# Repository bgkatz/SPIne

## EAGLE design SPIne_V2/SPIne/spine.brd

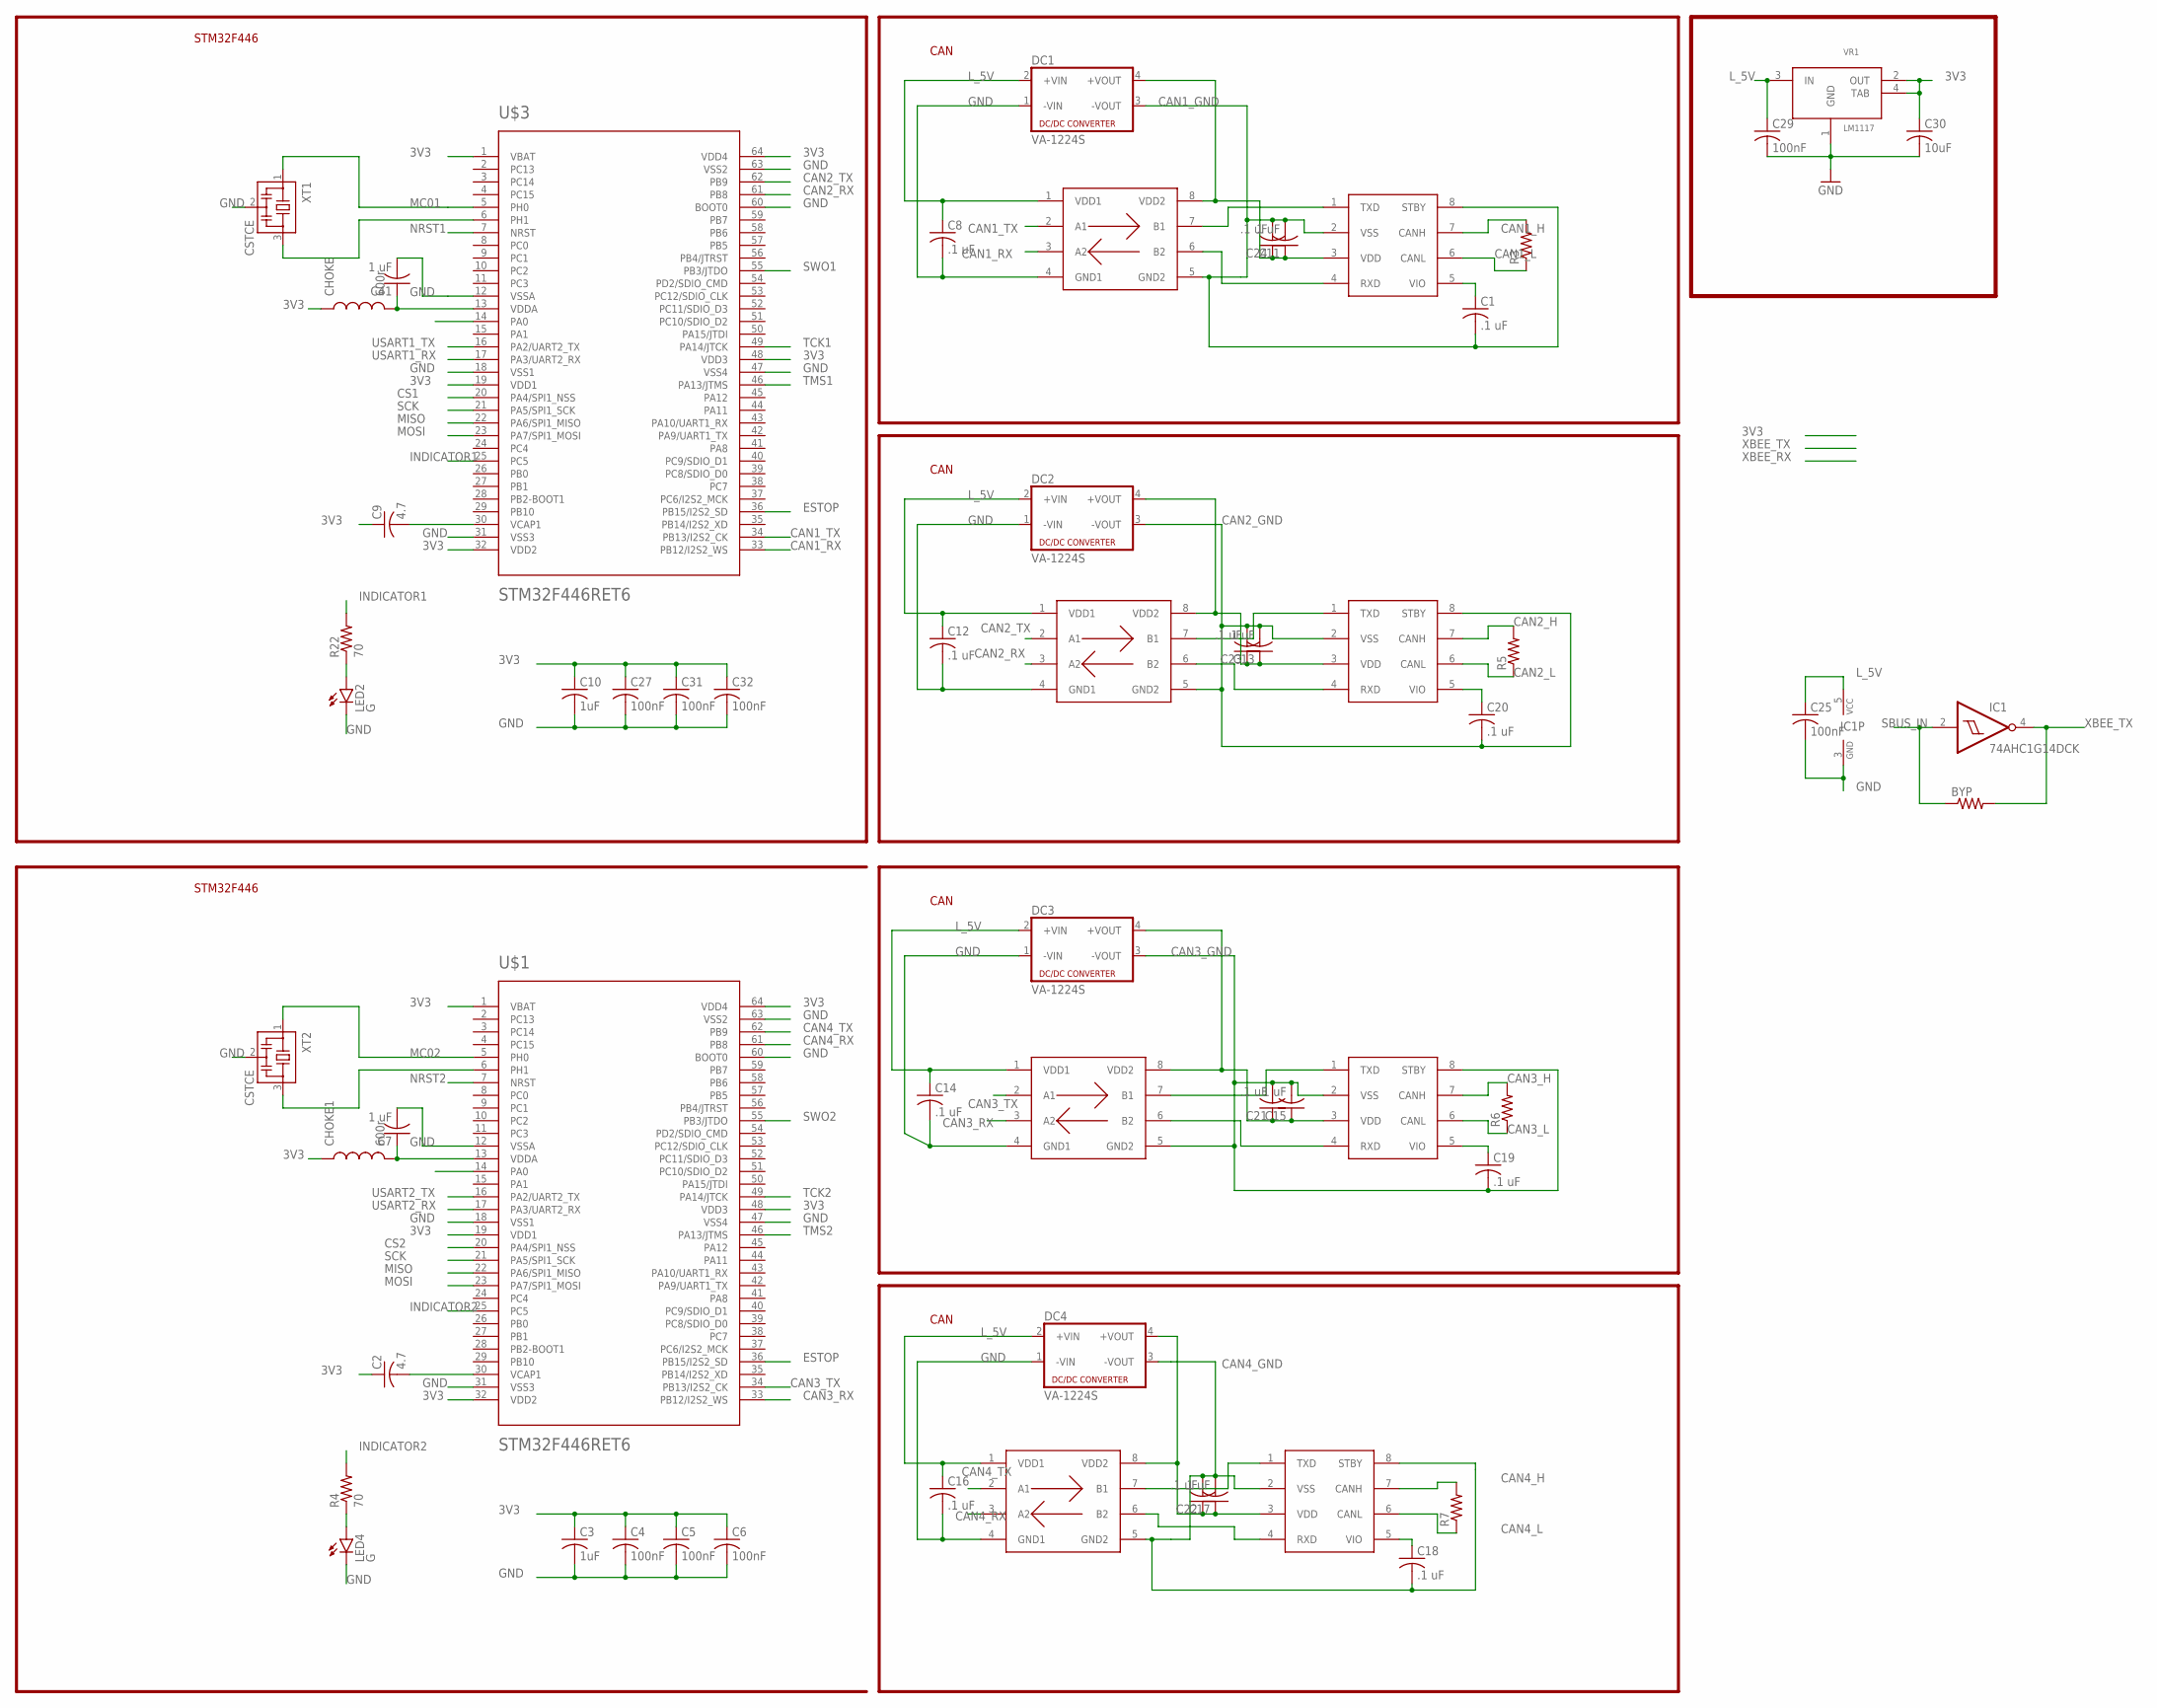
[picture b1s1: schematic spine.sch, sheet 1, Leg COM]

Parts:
BYP: R-US_R0402; R0402
C1, C8, C12, C14, C16, C18, C19, C20, C21, C22, C23, C24: .1 uF; C0603K
C2, C9: 4.7; C0603
C3, C10: 1uF; C0603
C4, C5, C6, C25, C27, C29, C31, C32: 100nF; C0603
C7, C41: 1 uF; C0603
C11, C13, C15, C17: 1 uF; C0603K
C30: 10uF; C0805K
CHOKE, CHOKE1: 600r; 0603
DC1, DC2, DC3, DC4: VA-1224S; 4SIL
IC1: 74AHC1G14DCK; SC70-5
LED2, LED4: G; LED-0603
R3, R5, R6, R7: R-US_R0402; R0402
R4, R22: 70; R0603
U$1, U$3: STM32F446RET6; TQFP64
U$4, U$5, U$6, U$7: MCP2561; SO08
U$8, U$9, U$10, U$11: SI8410; SO08
VR1: LM1117; SOT-223
XT1, XT2: CSTCE

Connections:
3V3: C2.1, C3.1, C4.1, C5.1, C6.1, C9.1, C10.1, C27.1, C30.1, C31.1, C32.1, CHOKE.1, CHOKE1.1, U$1.1 (VBAT), U$1.19 (VDD1), U$1.32 (VDD2), U$1.48 (VDD3), U$1.64 (VDD4), U$3.1 (VBAT), U$3.19 (VDD1), U$3.32 (VDD2), U$3.48 (VDD3), U$3.64 (VDD4), VR1.2 (OUT), VR1.4 (TAB); also elsewhere on the board
': C17.1, C22.1, DC4.4 (+VOUT), U$7.3 (VDD), U$11.8 (VDD2)
CAN1_GND: C1.2, C11.2, C24.2, DC1.3 (-VOUT), U$4.2 (VSS), U$4.8 (STBY), U$8.5 (GND2); also elsewhere on the board
CAN1_H: R3.2, U$4.7 (CANH); also elsewhere on the board
CAN1_L: R3.1, U$4.6 (CANL); also elsewhere on the board
CAN1_RX: U$3.33 (PB12/I2S2_WS), U$8.3 (A2)
CAN1_TX: U$3.34 (PB13/I2S2_CK), U$8.2 (A1)
CAN2_GND: C13.2, C20.2, C23.2, DC2.3 (-VOUT), U$5.2 (VSS), U$5.8 (STBY), U$10.5 (GND2); also elsewhere on the board
CAN2_H: R5.2, U$5.7 (CANH); also elsewhere on the board
CAN2_L: R5.1, U$5.6 (CANL); also elsewhere on the board
CAN2_RX: U$3.61 (PB8), U$10.3 (A2)
CAN2_TX: U$3.62 (PB9), U$10.2 (A1)
CAN3_GND: C15.2, C19.2, C21.2, DC3.3 (-VOUT), U$6.2 (VSS), U$6.8 (STBY), U$9.5 (GND2); also elsewhere on the board
CAN3_H: R6.2, U$6.7 (CANH); also elsewhere on the board
CAN3_L: R6.1, U$6.6 (CANL); also elsewhere on the board
CAN3_RX: U$1.33 (PB12/I2S2_WS), U$9.3 (A2)
CAN3_TX: U$1.34 (PB13/I2S2_CK), U$9.2 (A1)
CAN4_GND: C17.2, C18.2, C22.2, DC4.3 (-VOUT), U$7.2 (VSS), U$7.8 (STBY), U$11.5 (GND2); also elsewhere on the board
CAN4_H: R7.2, U$7.7 (CANH); also elsewhere on the board
CAN4_L: R7.1, U$7.6 (CANL); also elsewhere on the board
CAN4_RX: U$1.61 (PB8), U$11.3 (A2)
CAN4_TX: U$1.62 (PB9), U$11.2 (A1)
CS1: U$3.20 (PA4/SPI1_NSS); also elsewhere on the board
CS2: U$1.20 (PA4/SPI1_NSS); also elsewhere on the board
ESTOP: U$1.36 (PB15/I2S2_SD), U$3.36 (PB15/I2S2_SD); also elsewhere on the board
GND: C3.2, C4.2, C5.2, C6.2, C7.2, C8.2, C10.2, C12.2, C14.2, C16.2, C25.2, C27.2, C29.2, C30.2, C31.2, C32.2, C41.2, DC1.1 (-VIN), DC2.1 (-VIN), DC3.1 (-VIN), DC4.1 (-VIN), IC1.3 (GND), LED2.C, LED4.C, U$1.12 (VSSA), U$1.18 (VSS1), U$1.31 (VSS3), U$1.47 (VSS4), U$1.60 (BOOT0), U$1.63 (VSS2), U$3.12 (VSSA), U$3.18 (VSS1), U$3.31 (VSS3), U$3.47 (VSS4), U$3.60 (BOOT0), U$3.63 (VSS2), U$8.4 (GND1), U$9.4 (GND1), U$10.4 (GND1), U$11.4 (GND1), VR1.1 (GND), XT1.2, XT2.2; also elsewhere on the board
INDICATOR1: R22.2, U$3.25 (PC5)
INDICATOR2: R4.2, U$1.25 (PC5)
L_5V: C8.1, C12.1, C14.1, C16.1, C25.1, C29.1, DC1.2 (+VIN), DC2.2 (+VIN), DC3.2 (+VIN), DC4.2 (+VIN), IC1.5 (VCC), U$8.1 (VDD1), U$9.1 (VDD1), U$10.1 (VDD1), U$11.1 (VDD1), VR1.3 (IN); also elsewhere on the board
MC01: U$3.5 (PH0), XT1.1
MC02: U$1.5 (PH0), XT2.1
MISO: U$1.22 (PA6/SPI1_MISO), U$3.22 (PA6/SPI1_MISO); also elsewhere on the board
MOSI: U$1.23 (PA7/SPI1_MOSI), U$3.23 (PA7/SPI1_MOSI); also elsewhere on the board
unnamed: C41.1, CHOKE.2, U$3.13 (VDDA)
unnamed: C9.2, U$3.30 (VCAP1)
unnamed: C7.1, CHOKE1.2, U$1.13 (VDDA)
unnamed: C2.2, U$1.30 (VCAP1)
unnamed: C1.1, U$4.5 (VIO)
unnamed: LED4.A, R4.1
unnamed: U$1.6 (PH1), XT2.3
unnamed: C20.1, U$5.5 (VIO)
unnamed: C15.1, C21.1, DC3.4 (+VOUT), U$6.3 (VDD), U$9.8 (VDD2)
unnamed: C11.1, C24.1, DC1.4 (+VOUT), U$4.3 (VDD), U$8.8 (VDD2)
unnamed: U$4.1 (TXD), U$8.7 (B1)
unnamed: U$7.1 (TXD), U$11.7 (B1)
unnamed: U$4.4 (RXD), U$8.6 (B2)
unnamed: U$7.4 (RXD), U$11.6 (B2)
unnamed: C18.1, U$7.5 (VIO)
unnamed: C13.1, C23.1, DC2.4 (+VOUT), U$5.3 (VDD), U$10.8 (VDD2)
unnamed: U$5.1 (TXD), U$10.7 (B1)
unnamed: U$5.4 (RXD), U$10.6 (B2)
unnamed: C19.1, U$6.5 (VIO)
unnamed: U$6.1 (TXD), U$9.7 (B1)
unnamed: U$6.4 (RXD), U$9.6 (B2)
unnamed: LED2.A, R22.1
unnamed: U$3.6 (PH1), XT1.3
NRST1: U$3.7 (NRST); also elsewhere on the board
NRST2: U$1.7 (NRST); also elsewhere on the board
SBUS_IN: BYP.1, IC1.2 (I); also elsewhere on the board
SCK: U$1.21 (PA5/SPI1_SCK), U$3.21 (PA5/SPI1_SCK); also elsewhere on the board
SWO1: U$3.55 (PB3/JTDO)
SWO2: U$1.55 (PB3/JTDO)
TCK1: U$3.49 (PA14/JTCK); also elsewhere on the board
TCK2: U$1.49 (PA14/JTCK); also elsewhere on the board
TMS1: U$3.46 (PA13/JTMS); also elsewhere on the board
TMS2: U$1.46 (PA13/JTMS); also elsewhere on the board
USART1_RX: U$3.17 (PA3/UART2_RX); also elsewhere on the board
USART1_TX: U$3.16 (PA2/UART2_TX); also elsewhere on the board
USART2_RX: U$1.17 (PA3/UART2_RX); also elsewhere on the board
USART2_TX: U$1.16 (PA2/UART2_TX); also elsewhere on the board
XBEE_TX: BYP.2, IC1.4 (O); also elsewhere on the board

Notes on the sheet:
STM32F446
CAN

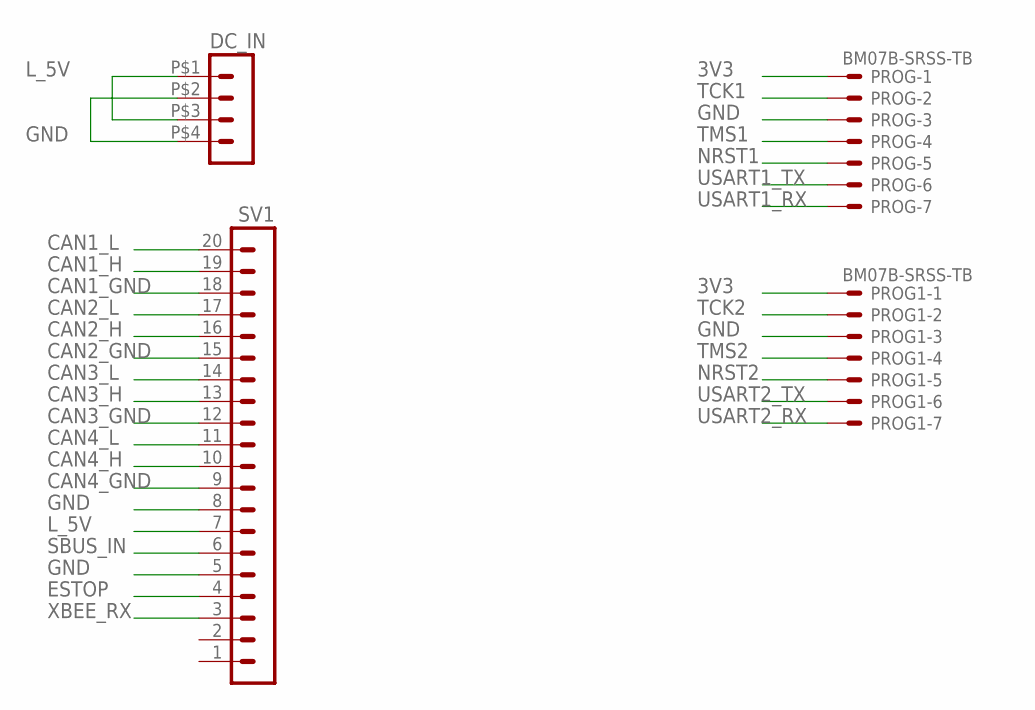
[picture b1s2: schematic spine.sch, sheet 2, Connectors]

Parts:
DC_IN: HEADER_POS4_43045-0401; 43045-0400
PROG, PROG1: BM07B-SRSS-TB
SV1: MA20-1L

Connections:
3V3: PROG.1, PROG1.1; also elsewhere on the board
CAN1_GND: SV1.18; also elsewhere on the board
CAN1_H: SV1.19; also elsewhere on the board
CAN1_L: SV1.20; also elsewhere on the board
CAN2_GND: SV1.15; also elsewhere on the board
CAN2_H: SV1.16; also elsewhere on the board
CAN2_L: SV1.17; also elsewhere on the board
CAN3_GND: SV1.12; also elsewhere on the board
CAN3_H: SV1.13; also elsewhere on the board
CAN3_L: SV1.14; also elsewhere on the board
CAN4_GND: SV1.9; also elsewhere on the board
CAN4_H: SV1.10; also elsewhere on the board
CAN4_L: SV1.11; also elsewhere on the board
ESTOP: SV1.4; also elsewhere on the board
GND: DC_IN.P$2 (2), DC_IN.P$4 (4), PROG.3, PROG1.3, SV1.5, SV1.8; also elsewhere on the board
L_5V: DC_IN.P$1 (1), DC_IN.P$3 (3), SV1.7; also elsewhere on the board
NRST1: PROG.5; also elsewhere on the board
NRST2: PROG1.5; also elsewhere on the board
SBUS_IN: SV1.6; also elsewhere on the board
TCK1: PROG.2; also elsewhere on the board
TCK2: PROG1.2; also elsewhere on the board
TMS1: PROG.4; also elsewhere on the board
TMS2: PROG1.4; also elsewhere on the board
USART1_RX: PROG.7; also elsewhere on the board
USART1_TX: PROG.6; also elsewhere on the board
USART2_RX: PROG1.7; also elsewhere on the board
USART2_TX: PROG1.6; also elsewhere on the board
XBEE_RX: SV1.3; also elsewhere on the board

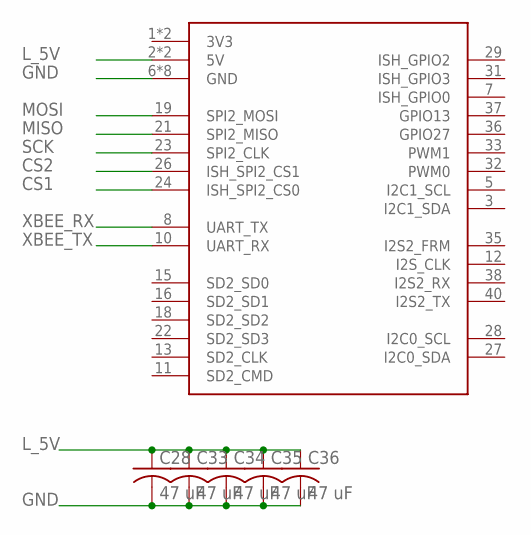
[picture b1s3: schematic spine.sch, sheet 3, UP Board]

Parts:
C28, C33, C34, C35, C36: 47 uF; C1206K
U$2: UP_BOARD

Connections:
CS1: U$2.24 (ISH_SPI2_CS0); also elsewhere on the board
CS2: U$2.26 (ISH_SPI2_CS1); also elsewhere on the board
GND: C28.2, C33.2, C34.2, C35.2, C36.2, U$2.6 (GND), U$2.9 (GND), U$2.14 (GND), U$2.20 (GND), U$2.25 (GND), U$2.30 (GND), U$2.34 (GND), U$2.39 (GND); also elsewhere on the board
L_5V: C28.1, C33.1, C34.1, C35.1, C36.1, U$2.2 (5V), U$2.4 (5V); also elsewhere on the board
MISO: U$2.21 (SPI2_MISO); also elsewhere on the board
MOSI: U$2.19 (SPI2_MOSI); also elsewhere on the board
SCK: U$2.23 (SPI2_CLK); also elsewhere on the board
XBEE_RX: U$2.8 (UART_TX); also elsewhere on the board
XBEE_TX: U$2.10 (UART_RX); also elsewhere on the board

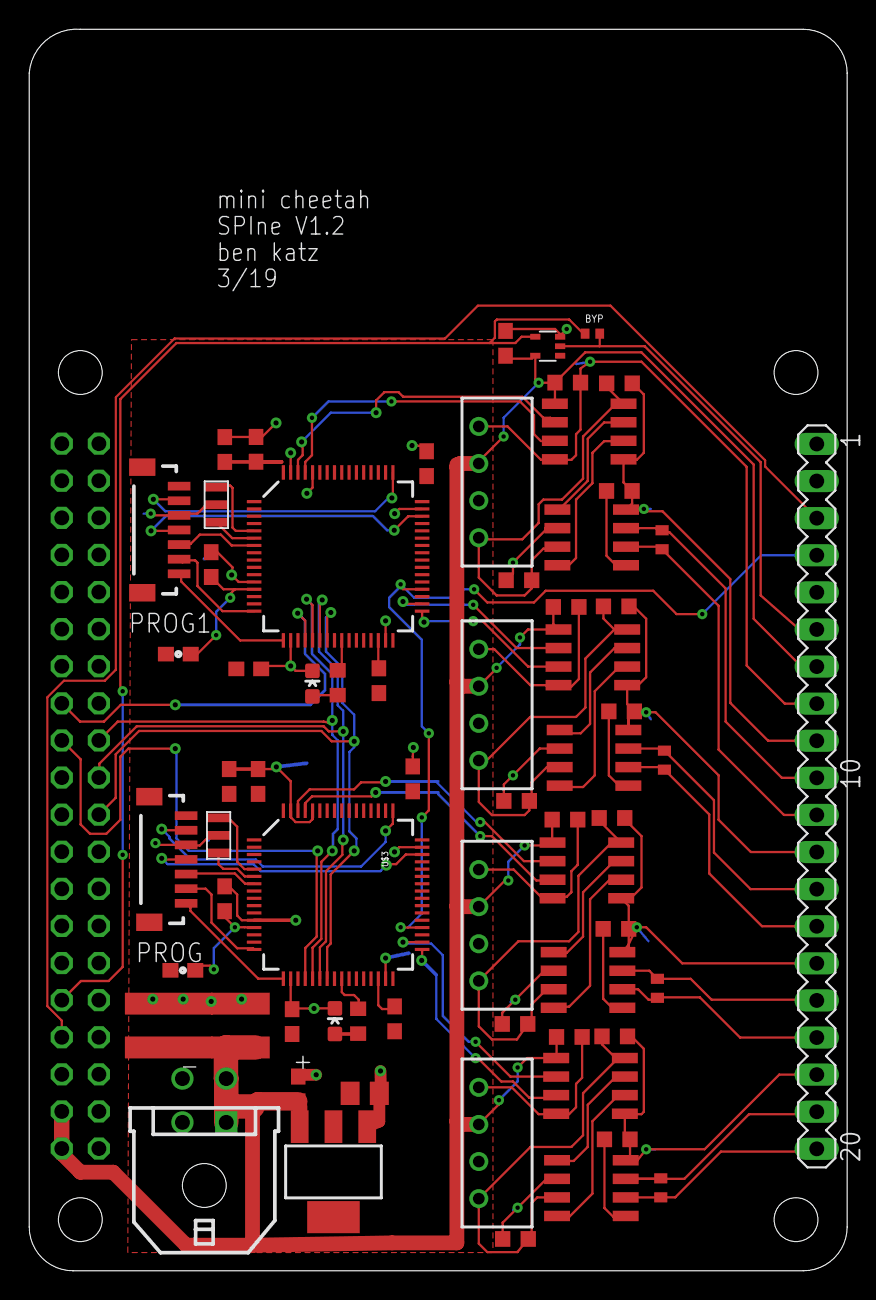
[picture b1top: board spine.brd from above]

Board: 2 copper layers, 56.0 x 85.0 mm, 70 parts (0 on the bottom side), 70 nets.

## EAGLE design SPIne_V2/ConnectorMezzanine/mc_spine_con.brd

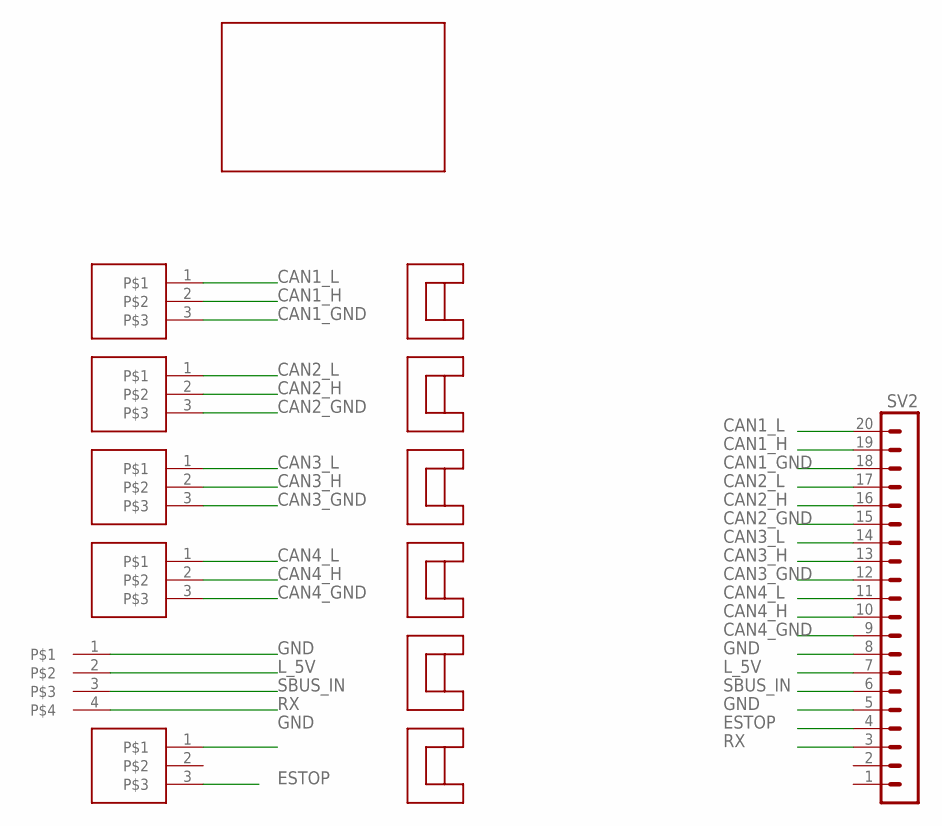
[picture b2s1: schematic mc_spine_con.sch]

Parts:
SV2: MA20-1L
U$1, U$3, U$4, U$6, U$12: 3-PIN; M80-8430342
U$2: UP_BOARD_NOPINS
U$5: 4-PIN; M80-8430442
U$7, U$8, U$9, U$10, U$11, U$13: SMD_CABLE_CLIPSS8111-46R; S8111-46R

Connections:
CAN1_GND: SV2.18, U$12.3
CAN1_H: SV2.19, U$12.2
CAN1_L: SV2.20, U$12.1
CAN2_GND: SV2.15, U$1.3
CAN2_H: SV2.16, U$1.2
CAN2_L: SV2.17, U$1.1
CAN3_GND: SV2.12, U$3.3
CAN3_H: SV2.13, U$3.2
CAN3_L: SV2.14, U$3.1
CAN4_GND: SV2.9, U$4.3
CAN4_H: SV2.10, U$4.2
CAN4_L: SV2.11, U$4.1
ESTOP: SV2.4, U$6.3
GND: SV2.5, SV2.8, U$5.1, U$6.1
L_5V: SV2.7, U$5.2
RX: SV2.3, U$5.4
SBUS_IN: SV2.6, U$5.3

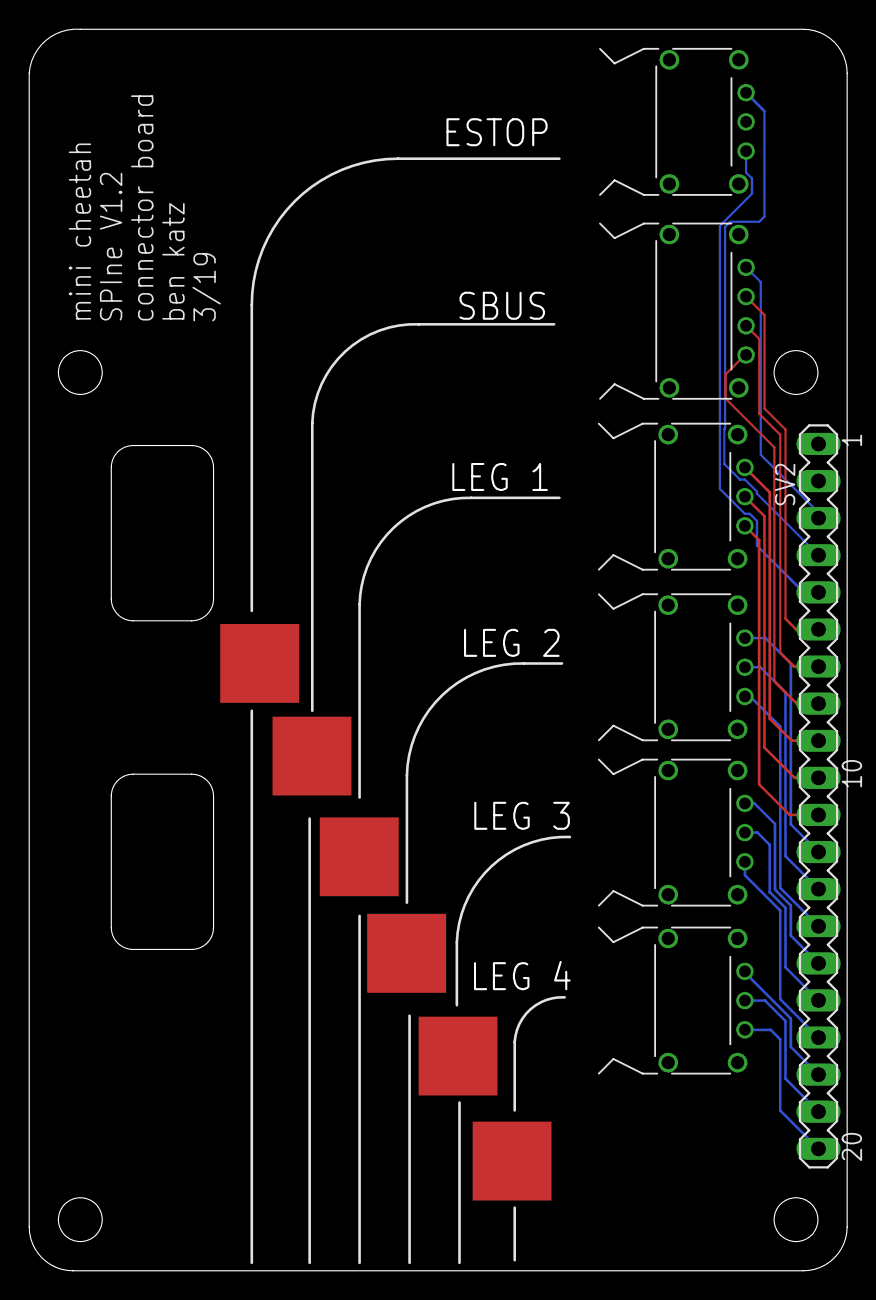
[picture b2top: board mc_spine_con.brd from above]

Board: 2 copper layers, 56.0 x 85.0 mm, 14 parts (0 on the bottom side), 17 nets.

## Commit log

2018-05-02 :lollipop: Added .gitattributes & .gitignore files
2018-05-02 Initial upload
2019-09-12 added latest version with separate strain-relieved connector board
2020-10-09 updated BOM

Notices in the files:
parts and their libraries:
SparkFun-Passives: Licensing: Creative Commons ShareAlike 4.0 International - https://creativecommons.org/licenses/by-sa/4.0
